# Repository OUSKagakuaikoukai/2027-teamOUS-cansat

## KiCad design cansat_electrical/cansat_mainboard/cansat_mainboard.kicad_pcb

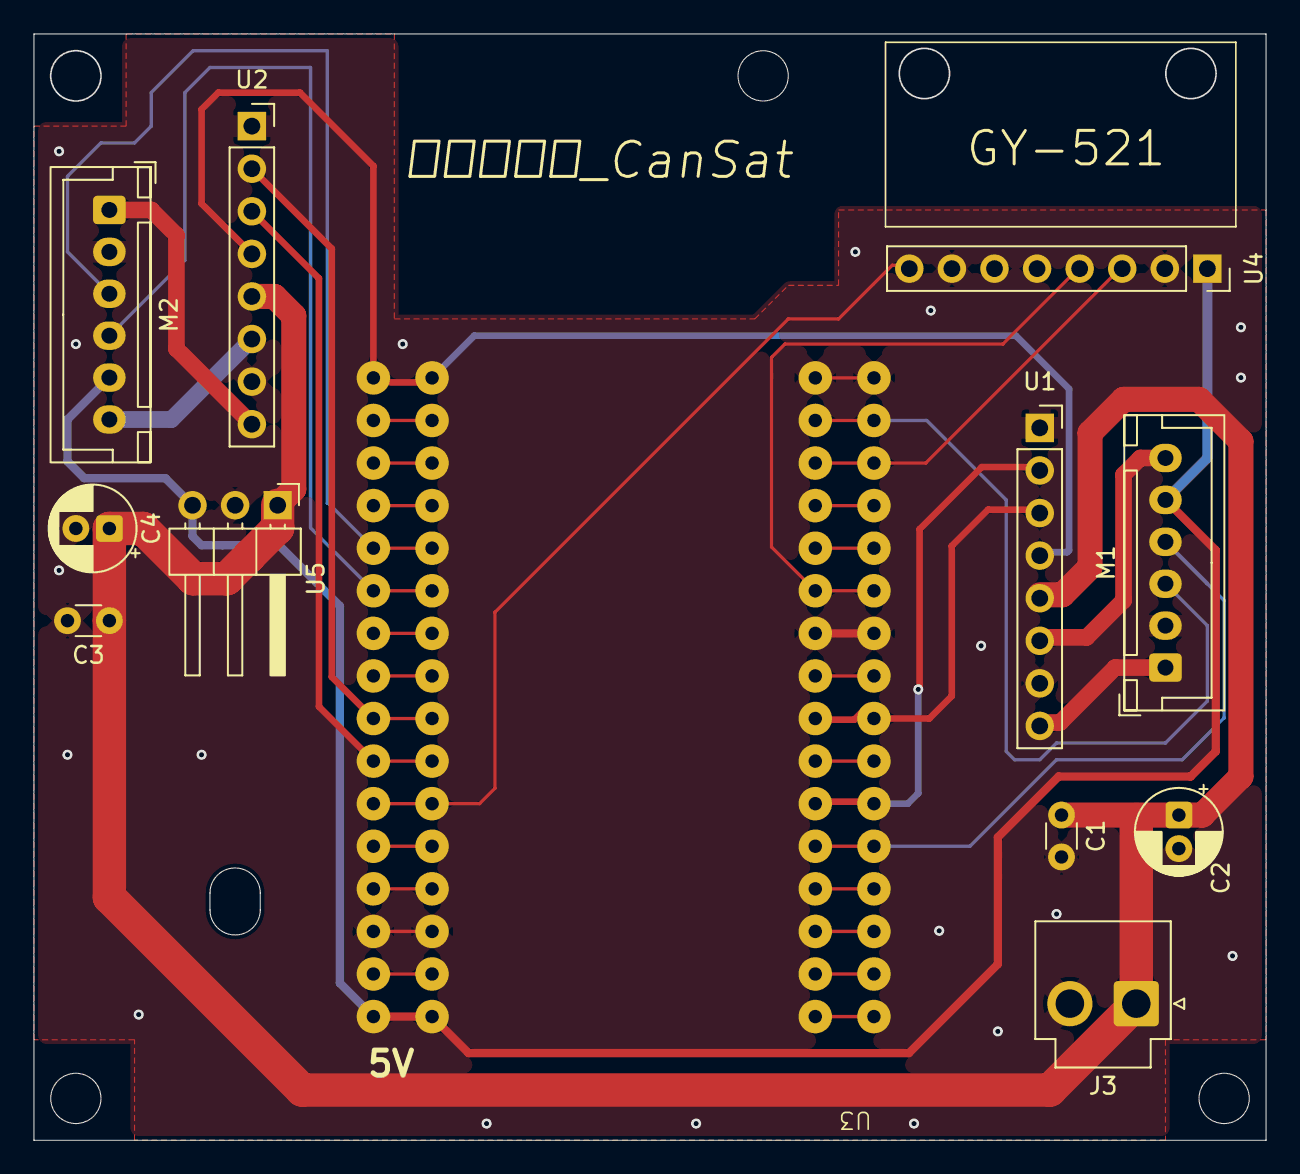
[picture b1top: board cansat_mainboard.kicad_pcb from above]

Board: 2 copper layers, 73.4 x 66.0 mm, 12 parts (0 on the bottom side), 19 nets.

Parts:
C1, C3: C; C_Disc_D3.0mm_W1.6mm_P2.50mm
C2, C4: C_Polarized; CP_Radial_D5.0mm_P2.00mm
J3: Conn_01x02_Pin; JST_VH_B2P-VH-B_1x02_P3.96mm_Vertical
M1, M2: JGA25-371 with encoder; JST_XH_B6B-XH-A_1x06_P2.50mm_Vertical
U1, U2, U4: PinSocket_1x08_P2.54mm_Vertical
U3: AE-ESP32-WROOM-32E-MINI
U5: PinHeader_1x03_P2.54mm_Horizontal

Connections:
+3V3: U1.4 (VREF), U2.4 (VREF), U3.16 (3V3)
+5V: M1.5 (Vcc), M2.5 (Vcc), U3.1 (5V), U4.1 (VCC), U5.3 (O)
/INT: U3.6 (27), U4.8 (INT)
/M1_SIG1: M1.3 (SIG1), U3.31 (23)
/M1_SIG2: M1.4 (SIG2), U3.21 (16)
/M2_SIG1: M2.3 (SIG1), U3.12 (34)
/M2_SIG2: M2.4 (SIG2), U3.11 (35)
GND: C1.2, C2.2, C3.2, C4.2, J3.2, M1.2 (GND), M2.2 (GND), U1.1 (GND), U1.7 (RS), U2.1 (GND), U2.7 (RS), U3.3 (GND), U3.26 (GND), U3.32 (GND), U4.2 (GND), U4.7 (ADO), U5.2 (G)
unnamed: M1.1 (M1), U1.8 (OUT2)
unnamed: M1.6 (M2), U1.6 (OUT1)
unnamed: M2.1 (M1), U2.8 (OUT2)
unnamed: M2.6 (M2), U2.6 (OUT1)
unnamed: U1.3 (IN1), U3.24 (18)
unnamed: U1.2 (IN2), U3.22 (17)
unnamed: U2.3 (IN1), U3.7 (26)
unnamed: U2.2 (IN2), U3.8 (25)
unnamed: U3.27 (21), U4.4 (SDA)
unnamed: U3.30 (22), U4.3 (SCL)
VCC: C1.1, C2.1, C3.1, C4.1, J3.1, U1.5 (VM), U2.5 (VM), U5.1 (I)

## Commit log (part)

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2026-06-19 仕様書.txtに各メンバーの役割を追記しました。
2026-06-24 PlatformIOのフォルダを作りました
2026-06-24 モータ関数を追加しました
2026-06-24 Move関数の入力値範囲についてコメントしました
2026-06-24 main.cppでモータ関数を動かす
2026-06-26 仕様書（メカ）.txt
2026-06-26 部品のデータシート表を追加しました
2026-06-26 正常に表示されるよう修正しました
2026-06-26 データシート表にESP32を追加しました
